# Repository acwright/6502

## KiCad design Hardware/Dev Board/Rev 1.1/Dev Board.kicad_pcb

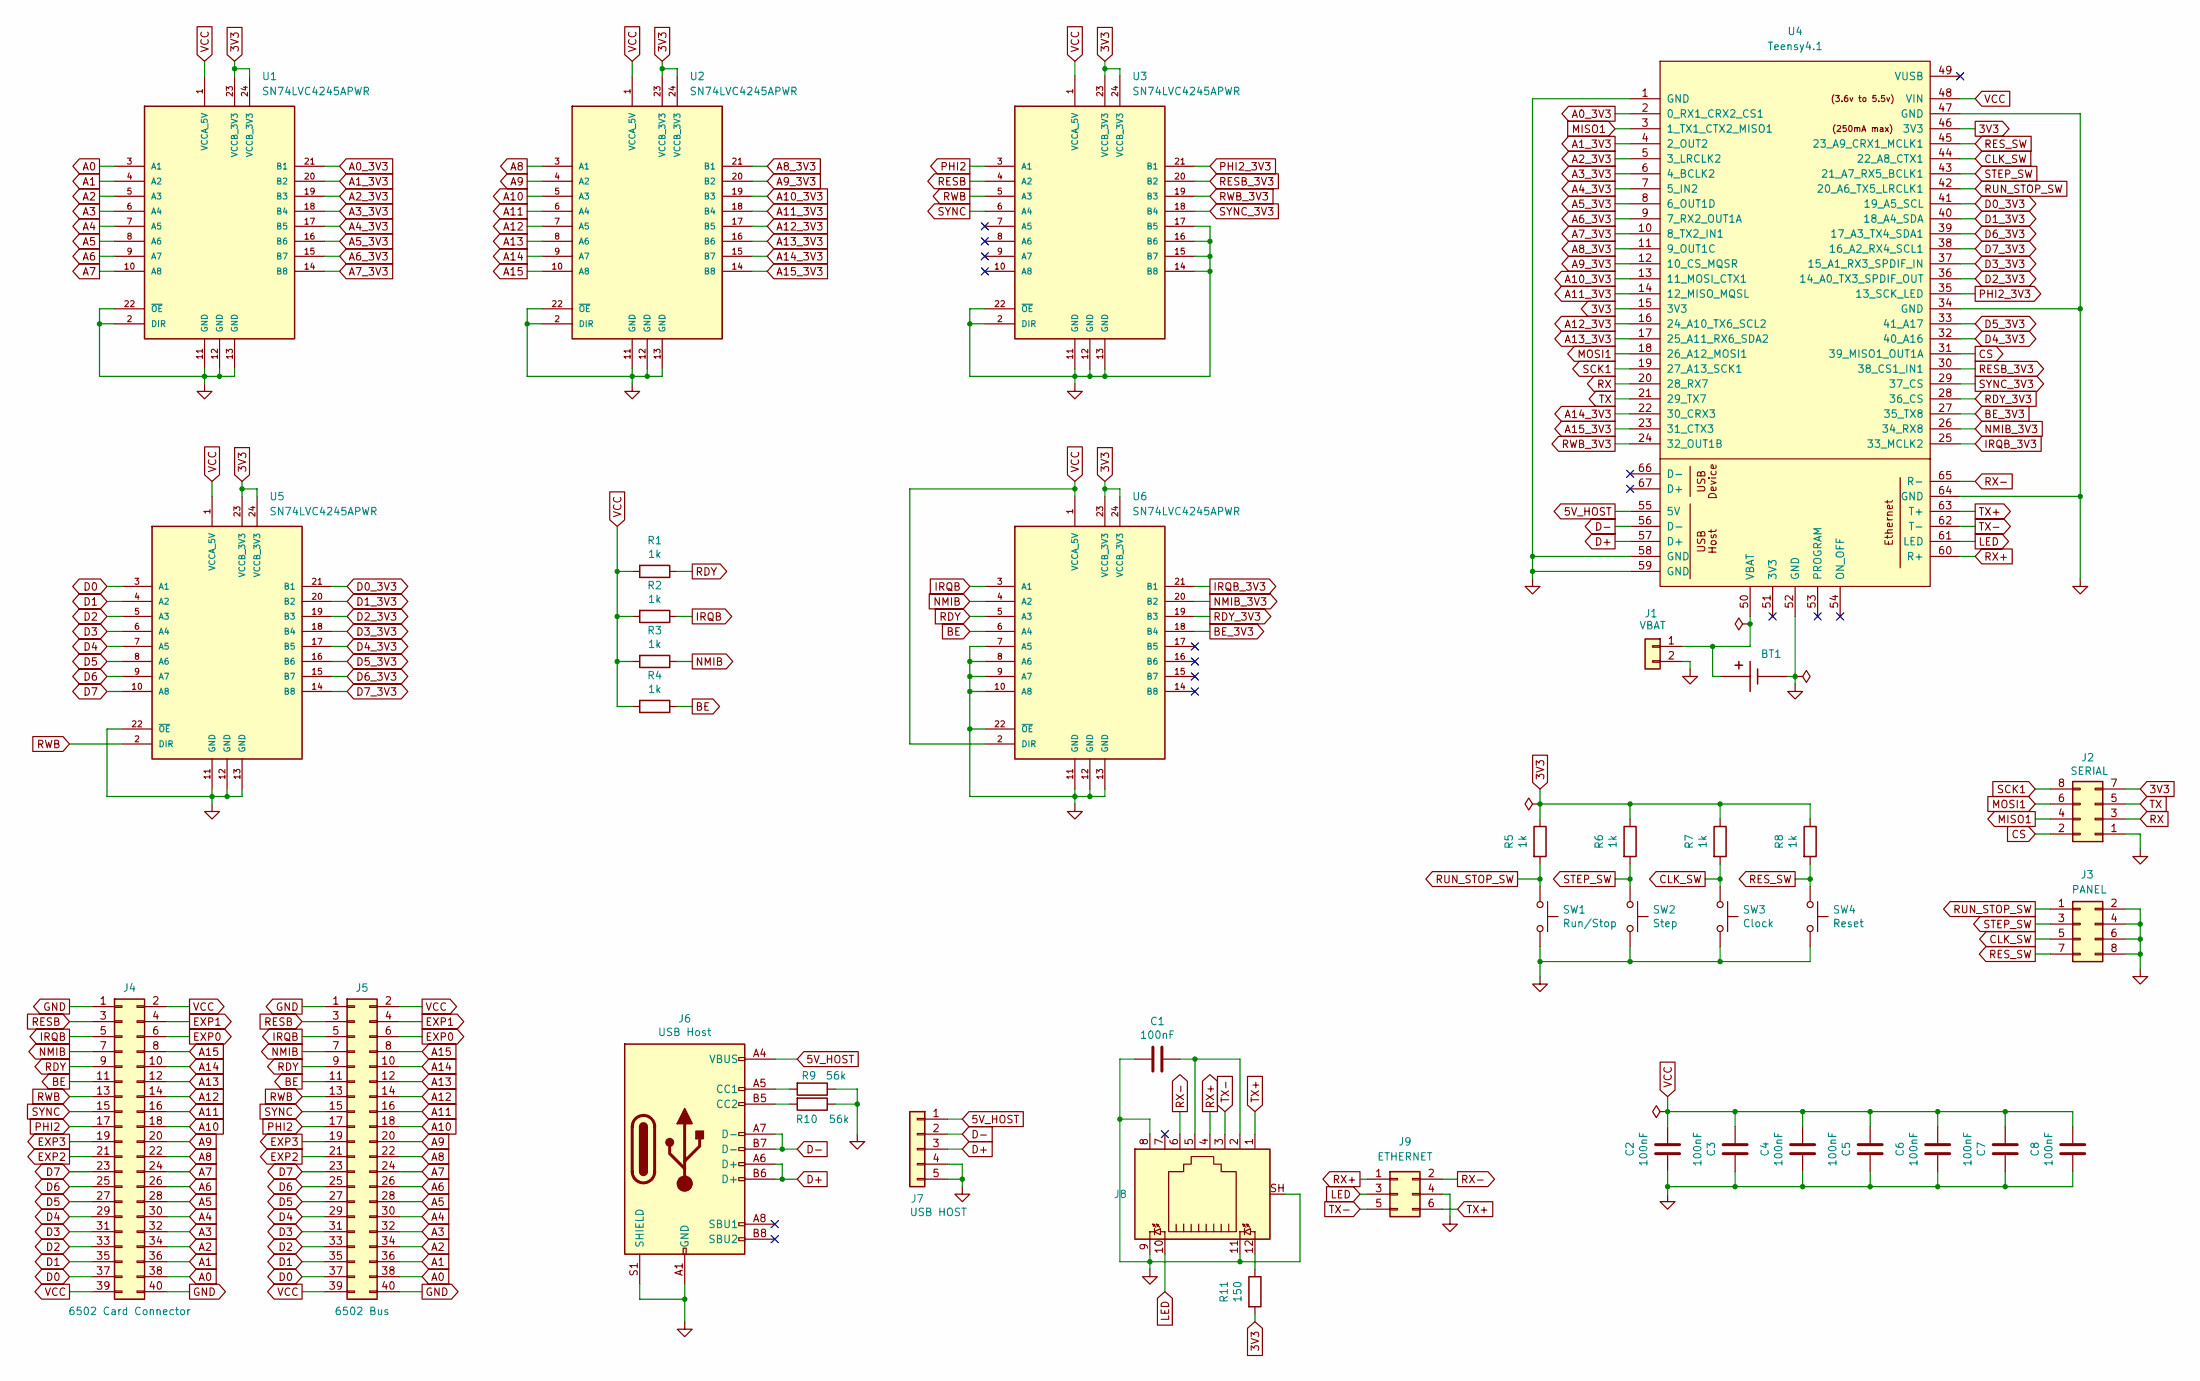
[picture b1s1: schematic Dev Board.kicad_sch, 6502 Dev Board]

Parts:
BT1: BAT-HLD-001-THM; BAT_BAT-HLD-001-THM
C1, C2, C3, C4, C5, C6, C7, C8: 100nF; C_0805_2012Metric; LCSC C49678
J1: VBAT; PinHeader_1x02_P2.54mm_Vertical
J2: SERIAL; PinHeader_2x04_P2.54mm_Vertical
J3: PANEL; PinHeader_2x04_P2.54mm_Vertical
J4: 6502 Card Connector; RHDR40W82P485X254_2X20_5740X93
J5: 6502 Bus; 6502 Bus Connector
J6: USB Host; USB_C_Receptacle_HRO_TYPE-C-31-M-12; LCSC C2988369
J7: USB HOST; PinHeader_1x05_P2.54mm_Vertical
J8: RJ45_LED; J1B1211CCD; MPN J1B1211CCD
J9: ETHERNET; PinHeader_2x03_P2.00mm_Vertical
R1, R2, R3, R4, R5, R6, R7, R8: 1k; R_0805_2012Metric; LCSC C17513
R9, R10: 56k; R_0805_2012Metric; LCSC C169923
R11: 150; R_0805_2012Metric; LCSC C17471
SW1: Run/Stop; SW_TS-1187A-B-A-B; LCSC C318884
SW2: Step; SW_TS-1187A-B-A-B; LCSC C318884
SW3: Clock; SW_TS-1187A-B-A-B; LCSC C318884
SW4: Reset; SW_TS-1187A-B-A-B; LCSC C318884
U1, U2, U3, U5, U6: SN74LVC4245APWR; TSSOP-24_4.4x7.8mm_P0.65mm; LCSC C7859
U4: Teensy4.1; Teensy41

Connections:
3V3: J2.7, R5.1, R6.1, R7.1, R8.1, R11.2, U1.23 (VCCB_3V3), U1.24 (VCCB_3V3), U2.23 (VCCB_3V3), U2.24 (VCCB_3V3), U3.23 (VCCB_3V3), U3.24 (VCCB_3V3), U4.15 (3V3), U4.46 (3V3), U5.23 (VCCB_3V3), U5.24 (VCCB_3V3), U6.23 (VCCB_3V3), U6.24 (VCCB_3V3)
5V_HOST: J6.A4 (VBUS), J6.A9 (VBUS), J6.B4 (VBUS), J6.B9 (VBUS), J7.1, U4.55 (5V)
A0: J4.38, J5.38, U1.3 (A1)
A0_3V3: U1.21 (B1), U4.2 (0_RX1_CRX2_CS1)
A1: J4.36, J5.36, U1.4 (A2)
A1_3V3: U1.20 (B2), U4.4 (2_OUT2)
A2: J4.34, J5.34, U1.5 (A3)
A2_3V3: U1.19 (B3), U4.5 (3_LRCLK2)
A3: J4.32, J5.32, U1.6 (A4)
A3_3V3: U1.18 (B4), U4.6 (4_BCLK2)
A4: J4.30, J5.30, U1.7 (A5)
A4_3V3: U1.17 (B5), U4.7 (5_IN2)
A5: J4.28, J5.28, U1.8 (A6)
A5_3V3: U1.16 (B6), U4.8 (6_OUT1D)
A6: J4.26, J5.26, U1.9 (A7)
A6_3V3: U1.15 (B7), U4.9 (7_RX2_OUT1A)
A7: J4.24, J5.24, U1.10 (A8)
A7_3V3: U1.14 (B8), U4.10 (8_TX2_IN1)
A8: J4.22, J5.22, U2.3 (A1)
A8_3V3: U2.21 (B1), U4.11 (9_OUT1C)
A9: J4.20, J5.20, U2.4 (A2)
A9_3V3: U2.20 (B2), U4.12 (10_CS_MQSR)
A10: J4.18, J5.18, U2.5 (A3)
A10_3V3: U2.19 (B3), U4.13 (11_MOSI_CTX1)
A11: J4.16, J5.16, U2.6 (A4)
A11_3V3: U2.18 (B4), U4.14 (12_MISO_MQSL)
A12: J4.14, J5.14, U2.7 (A5)
A12_3V3: U2.17 (B5), U4.16 (24_A10_TX6_SCL2)
A13: J4.12, J5.12, U2.8 (A6)
A13_3V3: U2.16 (B6), U4.17 (25_A11_RX6_SDA2)
A14: J4.10, J5.10, U2.9 (A7)
A14_3V3: U2.15 (B7), U4.22 (30_CRX3)
A15: J4.8, J5.8, U2.10 (A8)
A15_3V3: U2.14 (B8), U4.23 (31_CTX3)
BE: J4.11, J5.11, R4.1, U6.6 (A4)
BE_3V3: U4.27 (35_TX8), U6.18 (B4)
CLK_SW: J3.5, R7.2, SW3.1, U4.44 (22_A8_CTX1)
CS: J2.2, U4.31 (39_MISO1_OUT1A)
D0: J4.37, J5.37, U5.3 (A1)
D0_3V3: U4.41 (19_A5_SCL), U5.21 (B1)
D1: J4.35, J5.35, U5.4 (A2)
D1_3V3: U4.40 (18_A4_SDA), U5.20 (B2)
D2: J4.33, J5.33, U5.5 (A3)
D2_3V3: U4.36 (14_A0_TX3_SPDIF_OUT), U5.19 (B3)
D3: J4.31, J5.31, U5.6 (A4)
D3_3V3: U4.37 (15_A1_RX3_SPDIF_IN), U5.18 (B4)
D4: J4.29, J5.29, U5.7 (A5)
D4_3V3: U4.32 (40_A16), U5.17 (B5)
D5: J4.27, J5.27, U5.8 (A6)
D5_3V3: U4.33 (41_A17), U5.16 (B6)
D6: J4.25, J5.25, U5.9 (A7)
D6_3V3: U4.39 (17_A3_TX4_SDA1), U5.15 (B7)
D7: J4.23, J5.23, U5.10 (A8)
D7_3V3: U4.38 (16_A2_RX4_SCL1), U5.14 (B8)
D+: J6.A6 (D+), J6.B6 (D+), J7.3, U4.57 (D+)
D-: J6.A7 (D-), J6.B7 (D-), J7.2, U4.56 (D-)
EXP0: J4.6, J5.6
EXP1: J4.4, J5.4
EXP2: J4.21, J5.21
EXP3: J4.19, J5.19
GND: BT1.-, C1.2, C2.2, C3.1, C4.2, C5.1, C6.2, C7.1, C8.2, J1.2, J2.1, J3.2, J3.4, J3.6, J3.8, J4.1, J4.40, J5.1, J5.40, J6.A1 (GND), J6.A12 (GND), J6.B1 (GND), J6.B12 (GND), J6.S1 (SHIELD), J7.4, J7.5, J8.8, J8.9, J8.11, J8.SH, J9.4, R9.1, R10.1, SW1.2, SW2.2, SW3.2, SW4.2, U1.2 (DIR), U1.11 (GND), U1.12 (GND), U1.13 (GND), U1.22 (~OE), U2.2 (DIR), U2.11 (GND), U2.12 (GND), U2.13 (GND), U2.22 (~OE), U3.2 (DIR), U3.11 (GND), U3.12 (GND), U3.13 (GND), U3.14 (B8), U3.15 (B7), U3.16 (B6), U3.17 (B5), U3.22 (~OE), U4.1 (GND), U4.34 (GND), U4.47 (GND), U4.52 (GND), U4.58 (GND), U4.59 (GND), U4.64 (GND), U5.11 (GND), U5.12 (GND), U5.13 (GND), U5.22 (~OE), U6.7 (A5), U6.8 (A6), U6.9 (A7), U6.10 (A8), U6.11 (GND), U6.12 (GND), U6.13 (GND), U6.22 (~OE)
IRQB: J4.5, J5.5, R2.1, U6.3 (A1)
IRQB_3V3: U4.25 (33_MCLK2), U6.21 (B1)
LED: J8.10, J9.3, U4.61 (LED)
MISO1: J2.4, U4.3 (1_TX1_CTX2_MISO1)
MOSI1: J2.6, U4.18 (26_A12_MOSI1)
NMIB: J4.7, J5.7, R3.1, U6.4 (A2)
NMIB_3V3: U4.26 (34_RX8), U6.20 (B2)
unnamed: C1.1, J8.2, J8.5
unnamed: BT1.+, J1.1, U4.50 (VBAT)
unnamed: J6.A5 (CC1), R9.2
unnamed: J6.B5 (CC2), R10.2
unnamed: J8.12, R11.1
PHI2: J4.17, J5.17, U3.3 (A1)
PHI2_3V3: U3.21 (B1), U4.35 (13_SCK_LED)
RDY: J4.9, J5.9, R1.1, U6.5 (A3)
RDY_3V3: U4.28 (36_CS), U6.19 (B3)
RESB: J4.3, J5.3, U3.4 (A2)
RESB_3V3: U3.20 (B2), U4.30 (38_CS1_IN1)
RES_SW: J3.7, R8.2, SW4.1, U4.45 (23_A9_CRX1_MCLK1)
RUN_STOP_SW: J3.1, R5.2, SW1.1, U4.42 (20_A6_TX5_LRCLK1)
RWB: J4.13, J5.13, U3.5 (A3), U5.2 (DIR)
RWB_3V3: U3.19 (B3), U4.24 (32_OUT1B)
RX: J2.3, U4.20 (28_RX7)
RX+: J8.4, J9.1, U4.60 (R+)
RX-: J8.6, J9.2, U4.65 (R-)
SCK1: J2.8, U4.19 (27_A13_SCK1)
STEP_SW: J3.3, R6.2, SW2.1, U4.43 (21_A7_RX5_BCLK1)
SYNC: J4.15, J5.15, U3.6 (A4)
SYNC_3V3: U3.18 (B4), U4.29 (37_CS)
TX: J2.5, U4.21 (29_TX7)
TX+: J8.1, J9.6, U4.63 (T+)
TX-: J8.3, J9.5, U4.62 (T-)
VCC: C2.1, C3.2, C4.1, C5.2, C6.1, C7.2, C8.1, J4.2, J4.39, J5.2, J5.39, R1.2, R2.2, R3.2, R4.2, U1.1 (VCCA_5V), U2.1 (VCCA_5V), U3.1 (VCCA_5V), U4.48 (VIN), U5.1 (VCCA_5V), U6.1 (VCCA_5V), U6.2 (DIR)

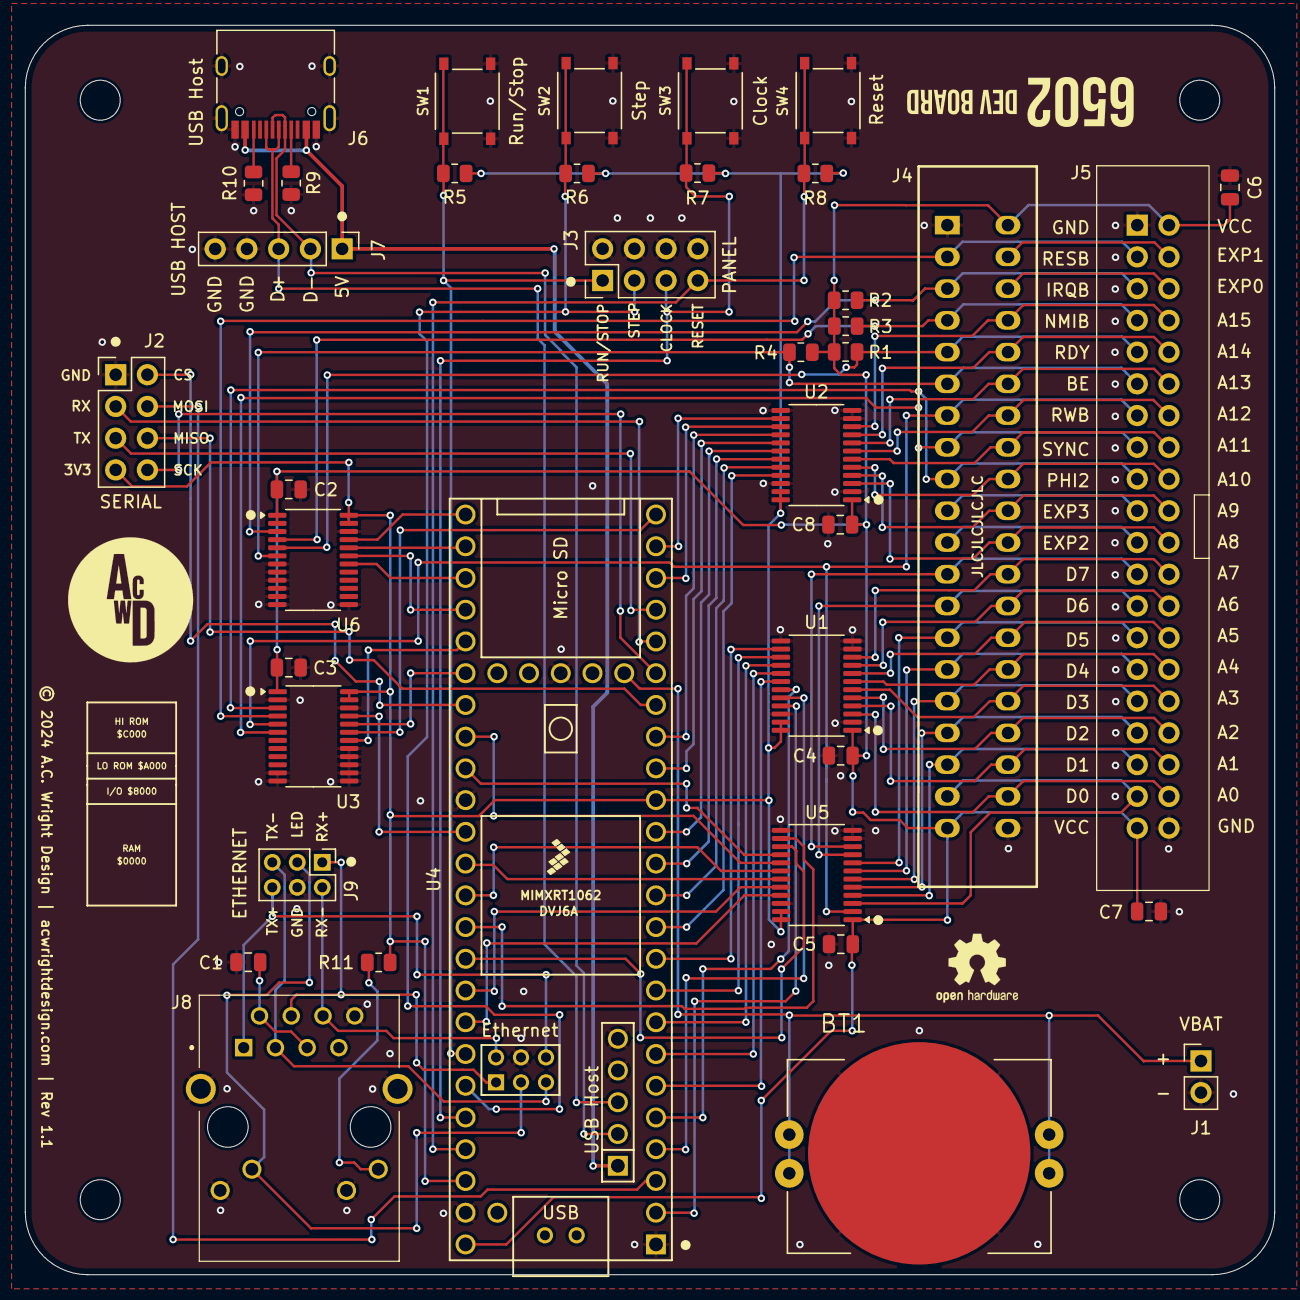
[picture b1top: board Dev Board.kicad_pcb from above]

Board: 2 copper layers, 100.0 x 100.0 mm, 43 parts (0 on the bottom side), 94 nets.

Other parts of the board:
H1, H2, H3, H4: MountingHole; MountingHole_3.2mm_M3

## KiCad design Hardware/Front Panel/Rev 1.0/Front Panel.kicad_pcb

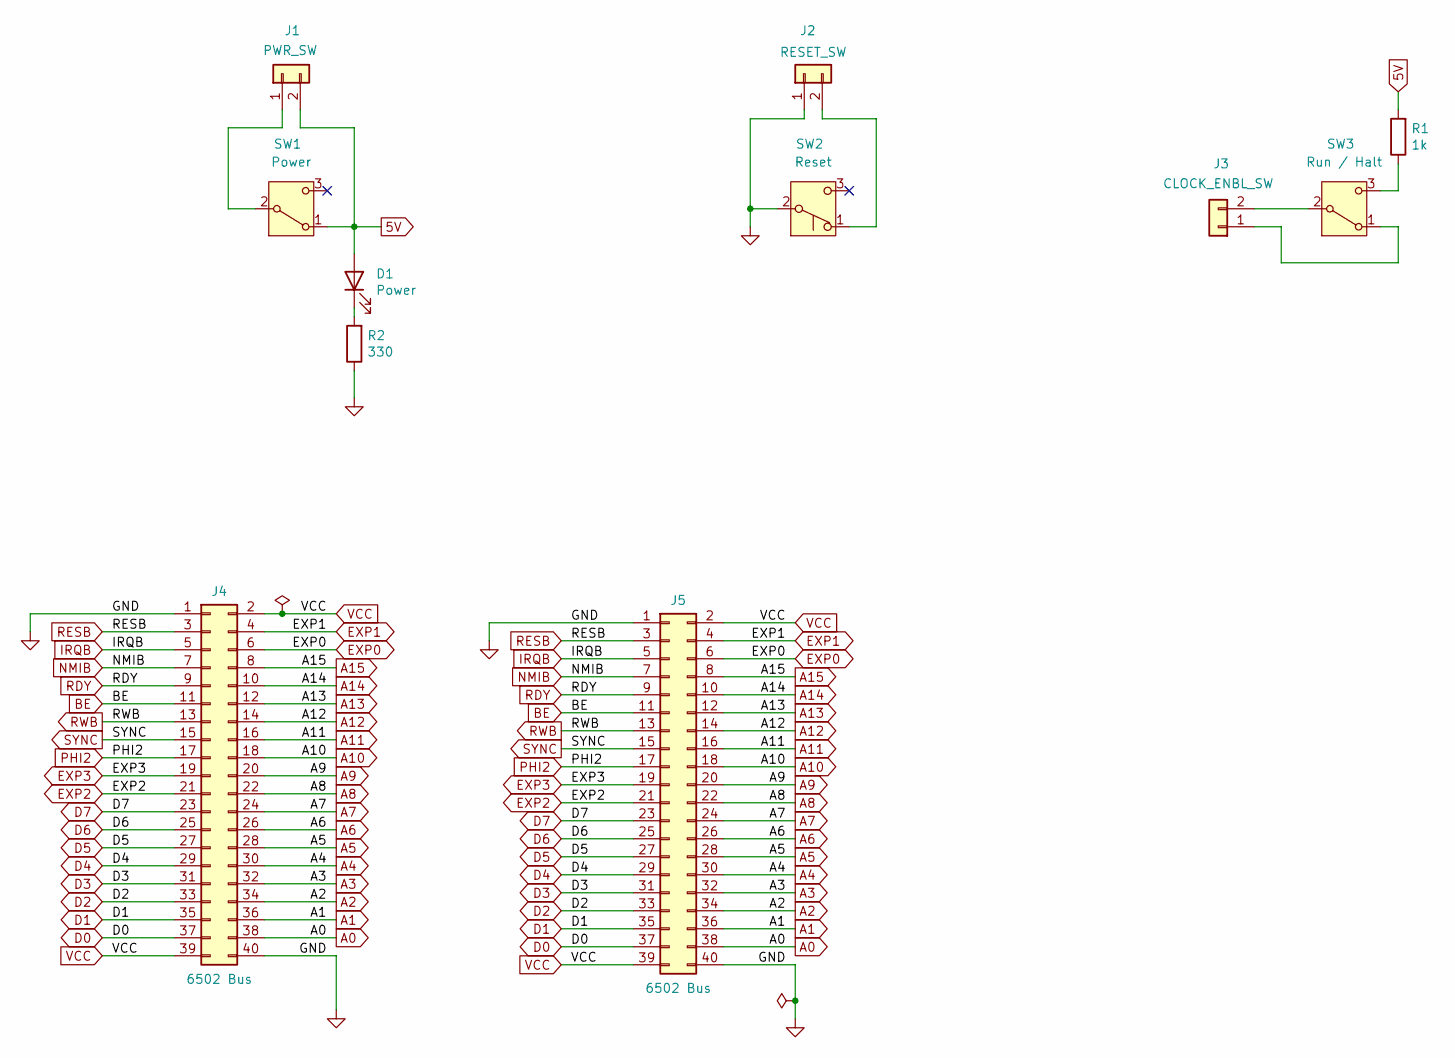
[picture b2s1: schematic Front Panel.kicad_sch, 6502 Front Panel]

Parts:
D1: Power; LED_D3.0mm; LCSC C2297
J1: PWR_SW; JST_XH_B2B-XH-A_1x02_P2.50mm_Vertical; Digikey 455-2247-ND
J2: RESET_SW; JST_XH_B2B-XH-A_1x02_P2.50mm_Vertical; Digikey 455-2247-ND
J3: CLOCK_ENBL_SW; JST_XH_B2B-XH-A_1x02_P2.50mm_Vertical; Digikey 455-2247-ND
J4, J5: 6502 Bus; 6502 Bus Connector
R1: 1k; R_Axial_DIN0207_L6.3mm_D2.5mm_P10.16mm_Horizontal; LCSC C17630
R2: 330; R_Axial_DIN0207_L6.3mm_D2.5mm_P10.16mm_Horizontal; LCSC C17630
SW1: Power; 300SP1J1BLKM2QE; MPN SS12D10; Mouser 612-300SP1J1BLKM2QE
SW2: Reset; 300SP1J1BLKM2QE; MPN SS12D10; Mouser 612-300SP2J1BLKM2QE
SW3: Run / Halt; 300SP1J1BLKM2QE; MPN SS12D10; Mouser 612-300SP1J1BLKM2QE

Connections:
5V: D1.2 (A), J1.2, R1.2, SW1.1 (A)
A0: J4.38, J5.38
A1: J4.36, J5.36
A2: J4.34, J5.34
A3: J4.32, J5.32
A4: J4.30, J5.30
A5: J4.28, J5.28
A6: J4.26, J5.26
A7: J4.24, J5.24
A8: J4.22, J5.22
A9: J4.20, J5.20
A10: J4.18, J5.18
A11: J4.16, J5.16
A12: J4.14, J5.14
A13: J4.12, J5.12
A14: J4.10, J5.10
A15: J4.8, J5.8
BE: J4.11, J5.11
D0: J4.37, J5.37
D1: J4.35, J5.35
D2: J4.33, J5.33
D3: J4.31, J5.31
D4: J4.29, J5.29
D5: J4.27, J5.27
D6: J4.25, J5.25
D7: J4.23, J5.23
EXP0: J4.6, J5.6
EXP1: J4.4, J5.4
EXP2: J4.21, J5.21
EXP3: J4.19, J5.19
GND: J2.1, J4.1, J4.40, J5.1, J5.40, R2.1, SW2.2 (B)
IRQB: J4.5, J5.5
NMIB: J4.7, J5.7
unnamed: D1.1 (K), R2.2
unnamed: J1.1, SW1.2 (B)
unnamed: J2.2, SW2.1 (A)
unnamed: J3.1, SW3.1 (A)
unnamed: J3.2, SW3.2 (B)
unnamed: R1.1, SW3.3 (C)
PHI2: J4.17, J5.17
RDY: J4.9, J5.9
RESB: J4.3, J5.3
RWB: J4.13, J5.13
SYNC: J4.15, J5.15
VCC: J4.2, J4.39, J5.2, J5.39

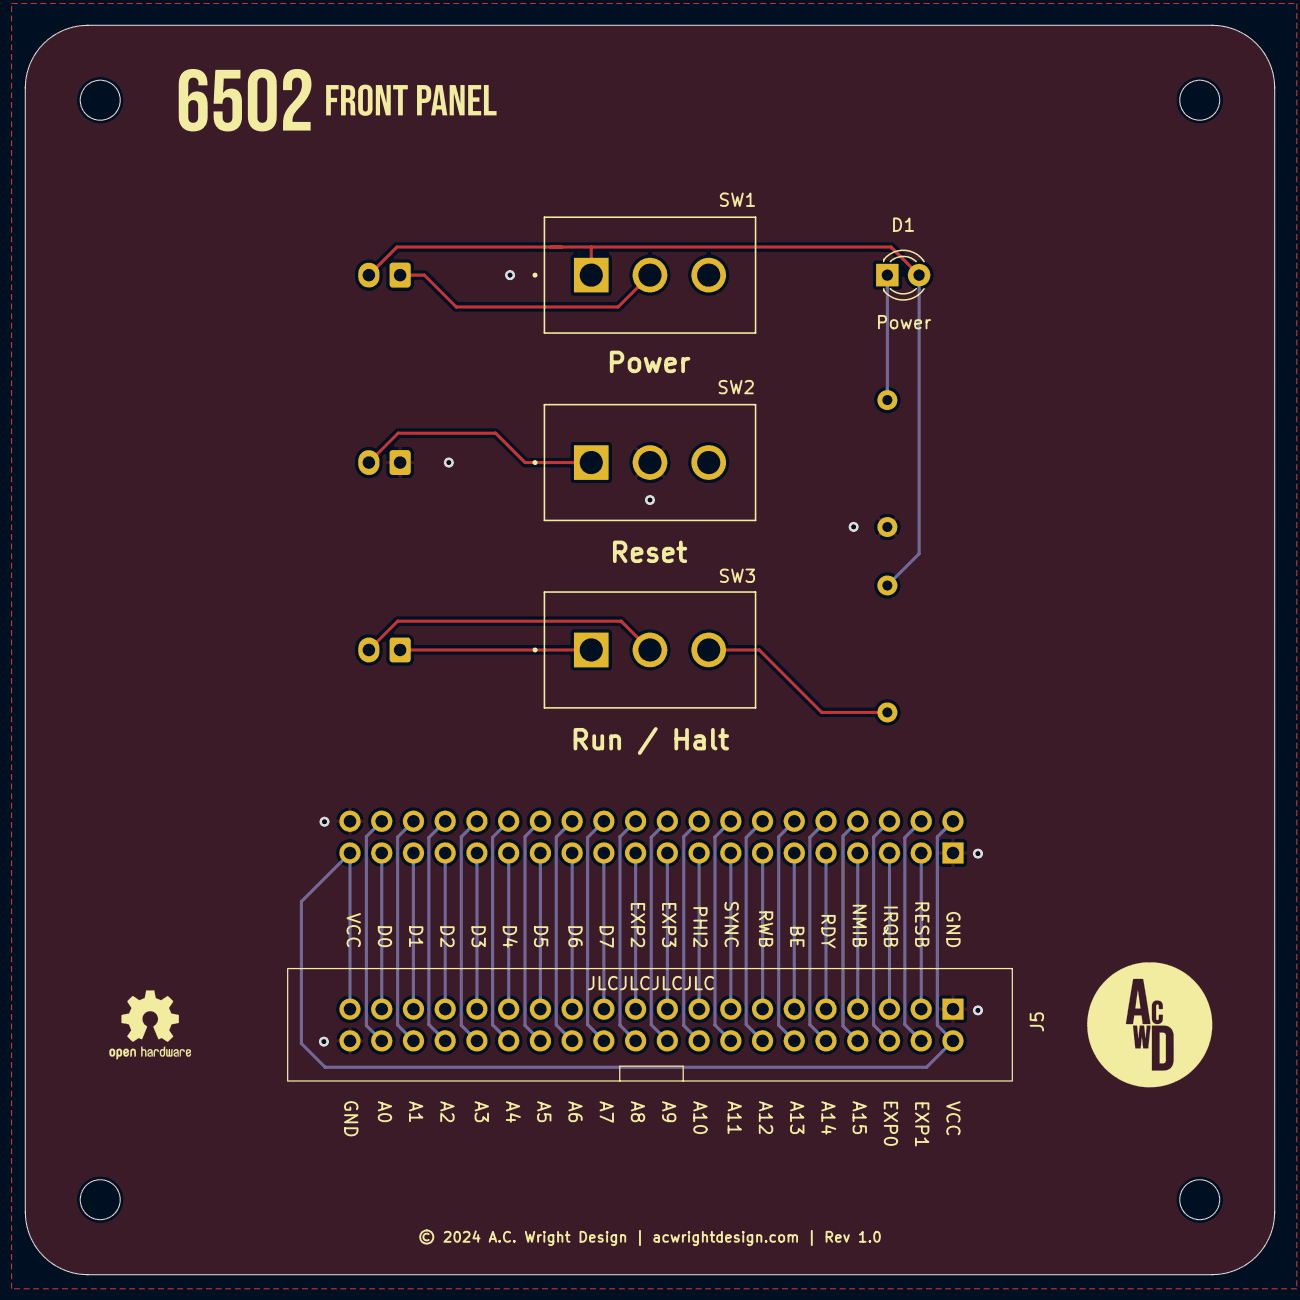
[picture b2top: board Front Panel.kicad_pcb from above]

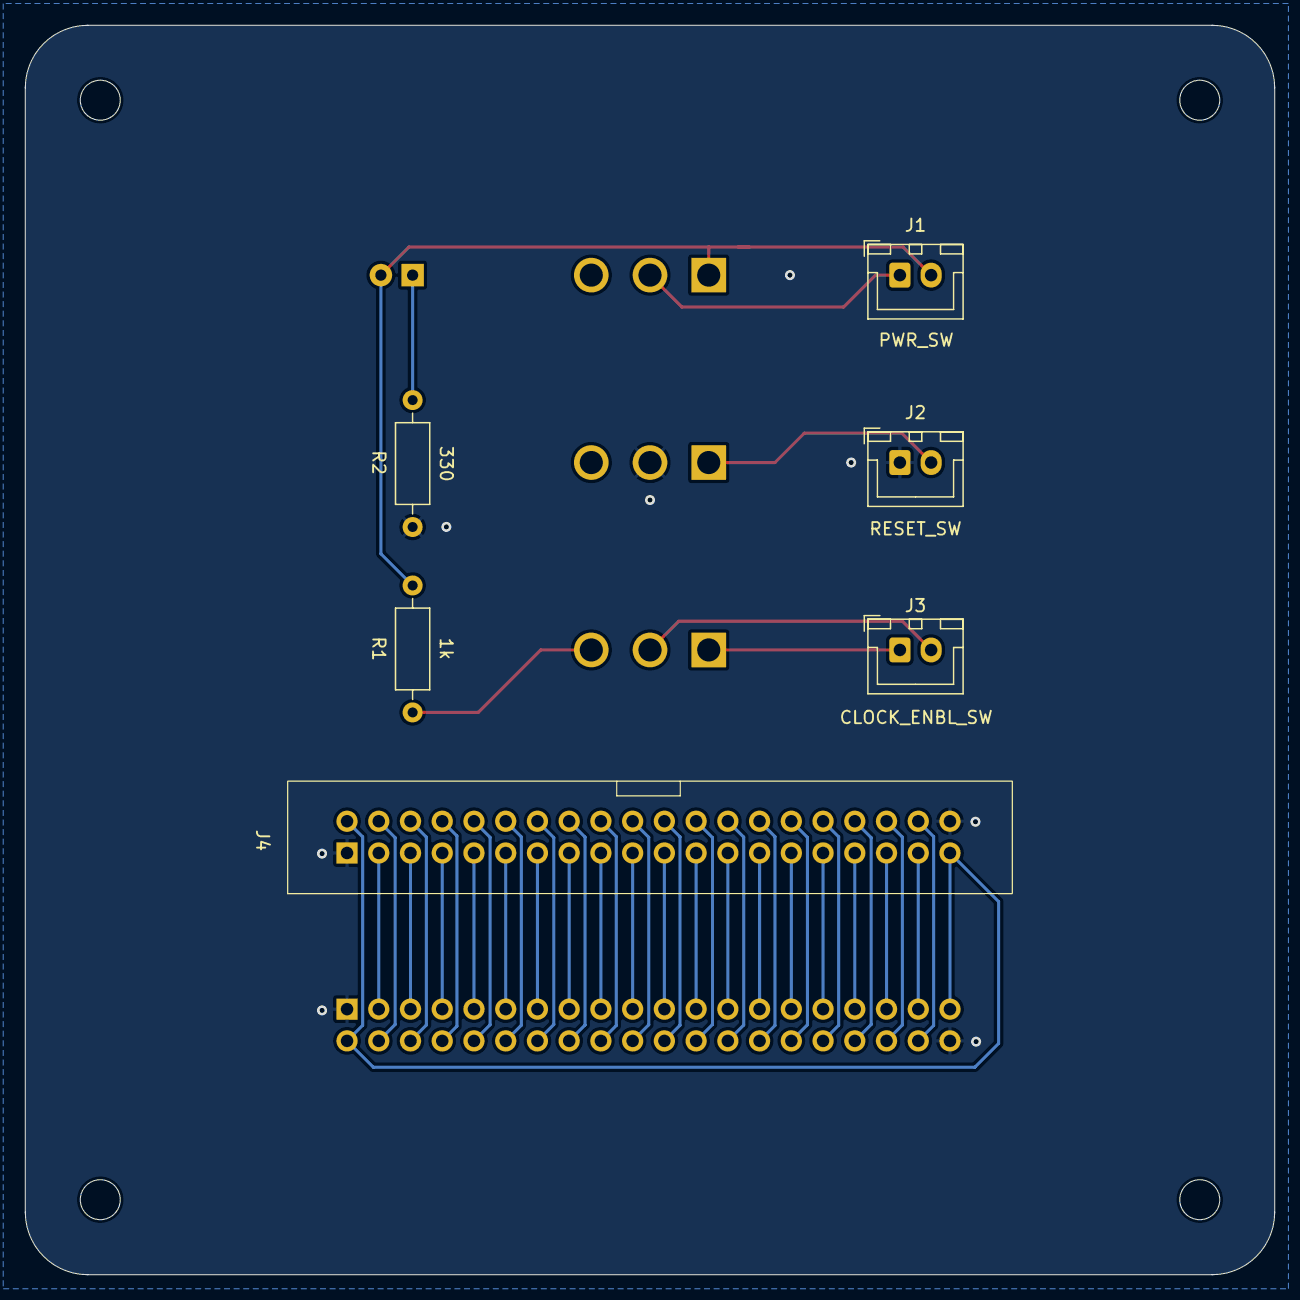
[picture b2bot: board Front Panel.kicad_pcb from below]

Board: 2 copper layers, 100.0 x 100.0 mm, 15 parts (6 on the bottom side), 45 nets.

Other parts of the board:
H1, H2, H3, H4: MountingHole; MountingHole_3.2mm_M3

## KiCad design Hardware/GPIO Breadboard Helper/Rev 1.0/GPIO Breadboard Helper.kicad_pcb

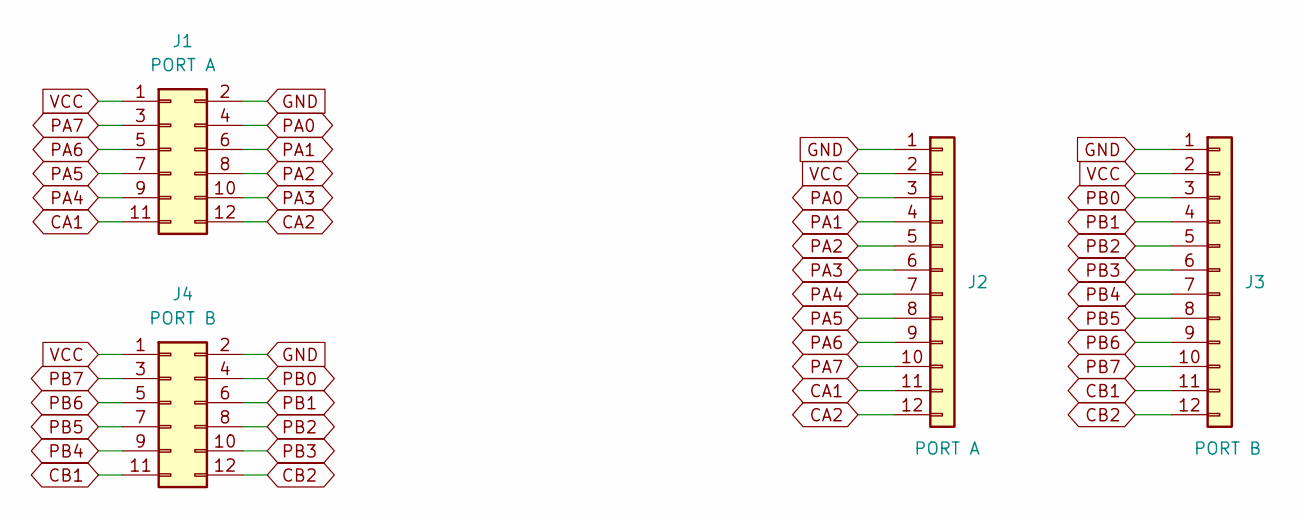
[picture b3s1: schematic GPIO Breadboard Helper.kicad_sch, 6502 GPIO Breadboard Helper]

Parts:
J1: PORT A; 6502 GPIO Connector
J2: PORT A; PinHeader_1x12_P2.54mm_Vertical
J3: PORT B; PinHeader_1x12_P2.54mm_Vertical
J4: PORT B; 6502 GPIO Connector

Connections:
CA1: J1.11, J2.11
CA2: J1.12, J2.12
CB1: J3.11, J4.11
CB2: J3.12, J4.12
GND: J1.2, J2.1, J3.1, J4.2
PA0: J1.4, J2.3
PA1: J1.6, J2.4
PA2: J1.8, J2.5
PA3: J1.10, J2.6
PA4: J1.9, J2.7
PA5: J1.7, J2.8
PA6: J1.5, J2.9
PA7: J1.3, J2.10
PB0: J3.3, J4.4
PB1: J3.4, J4.6
PB2: J3.5, J4.8
PB3: J3.6, J4.10
PB4: J3.7, J4.9
PB5: J3.8, J4.7
PB6: J3.9, J4.5
PB7: J3.10, J4.3
VCC: J1.1, J2.2, J3.2, J4.1

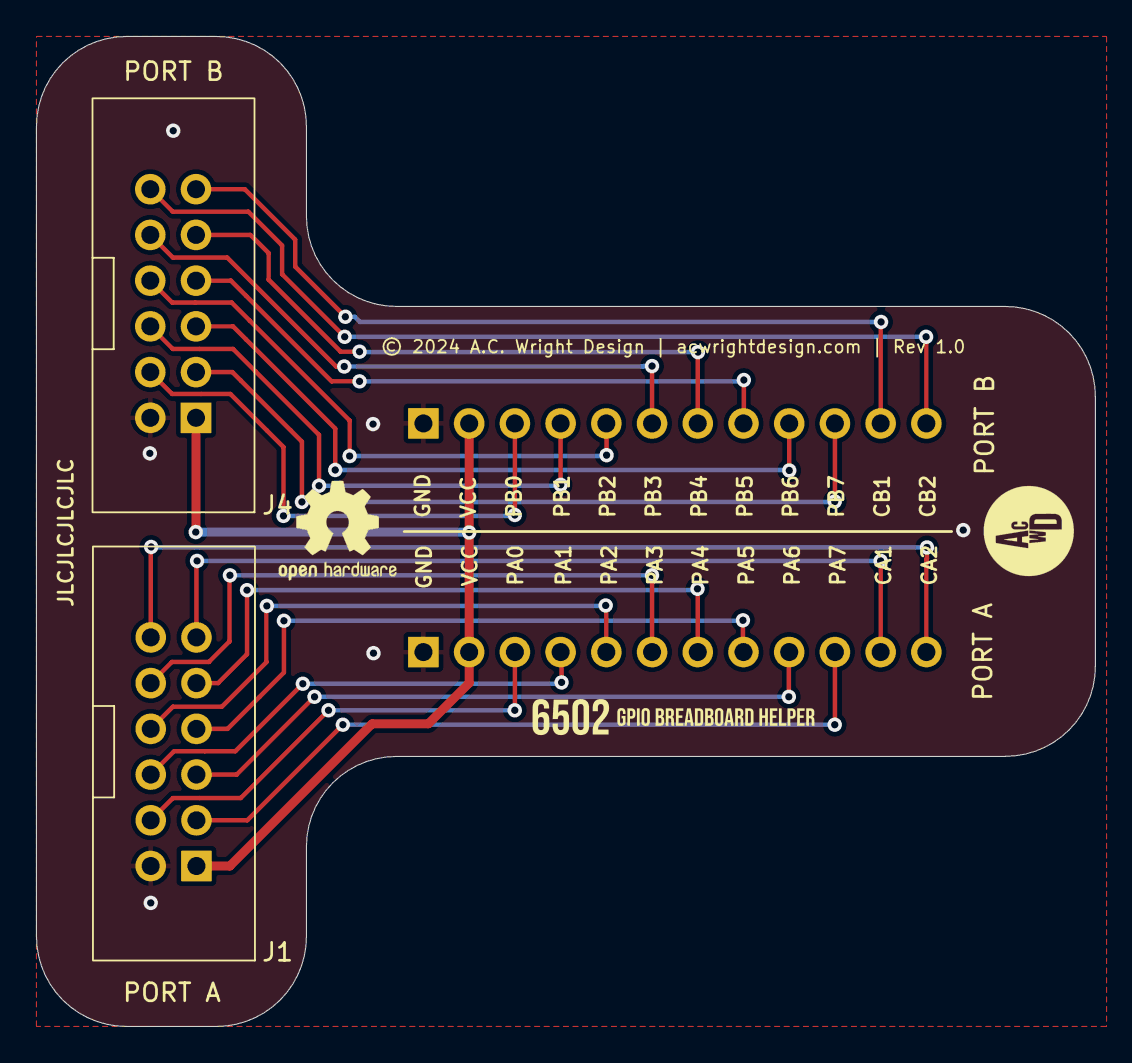
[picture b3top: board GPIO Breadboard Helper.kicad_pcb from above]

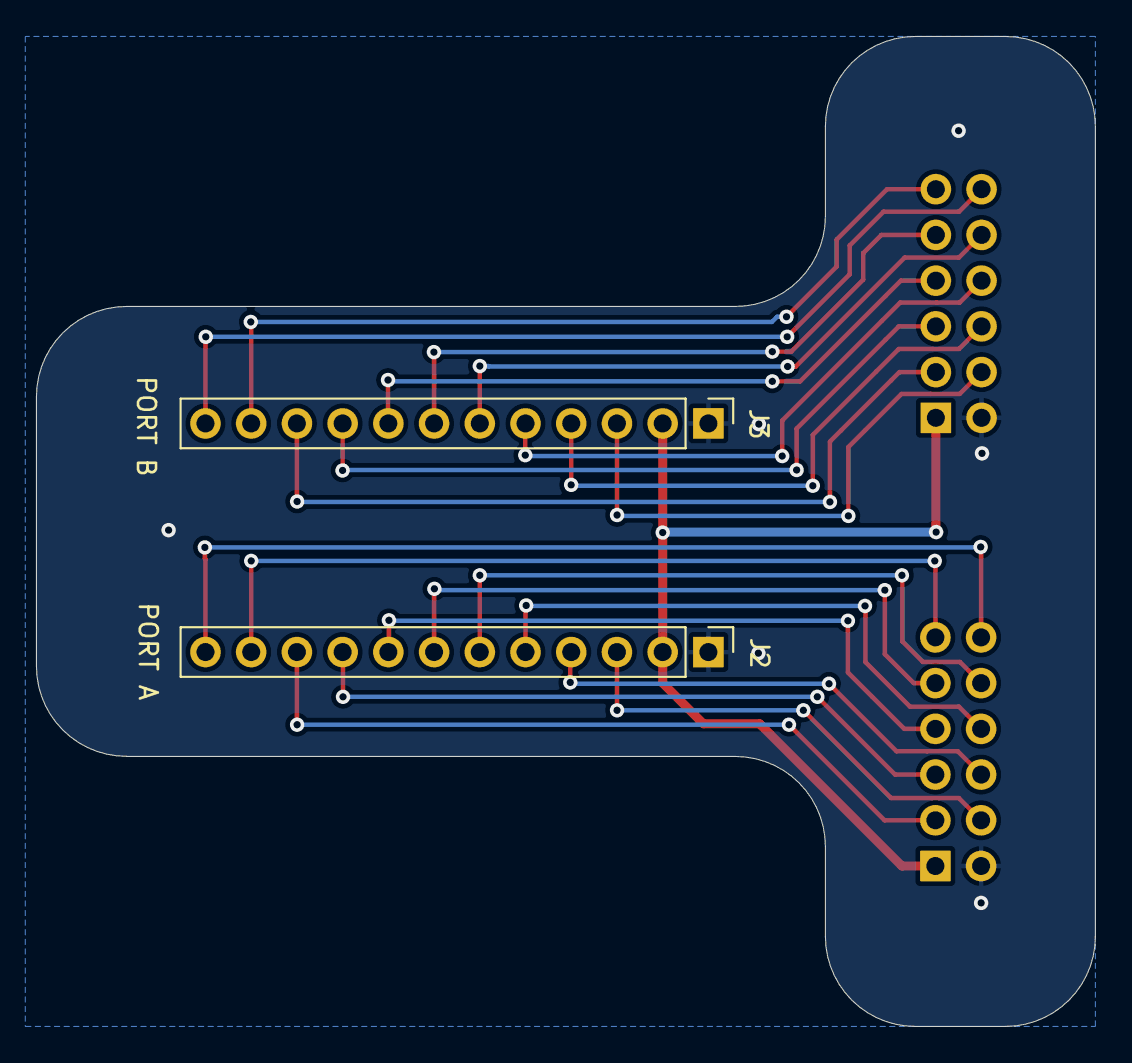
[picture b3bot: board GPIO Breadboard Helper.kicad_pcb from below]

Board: 2 copper layers, 58.8 x 55.0 mm, 4 parts (2 on the bottom side), 22 nets.

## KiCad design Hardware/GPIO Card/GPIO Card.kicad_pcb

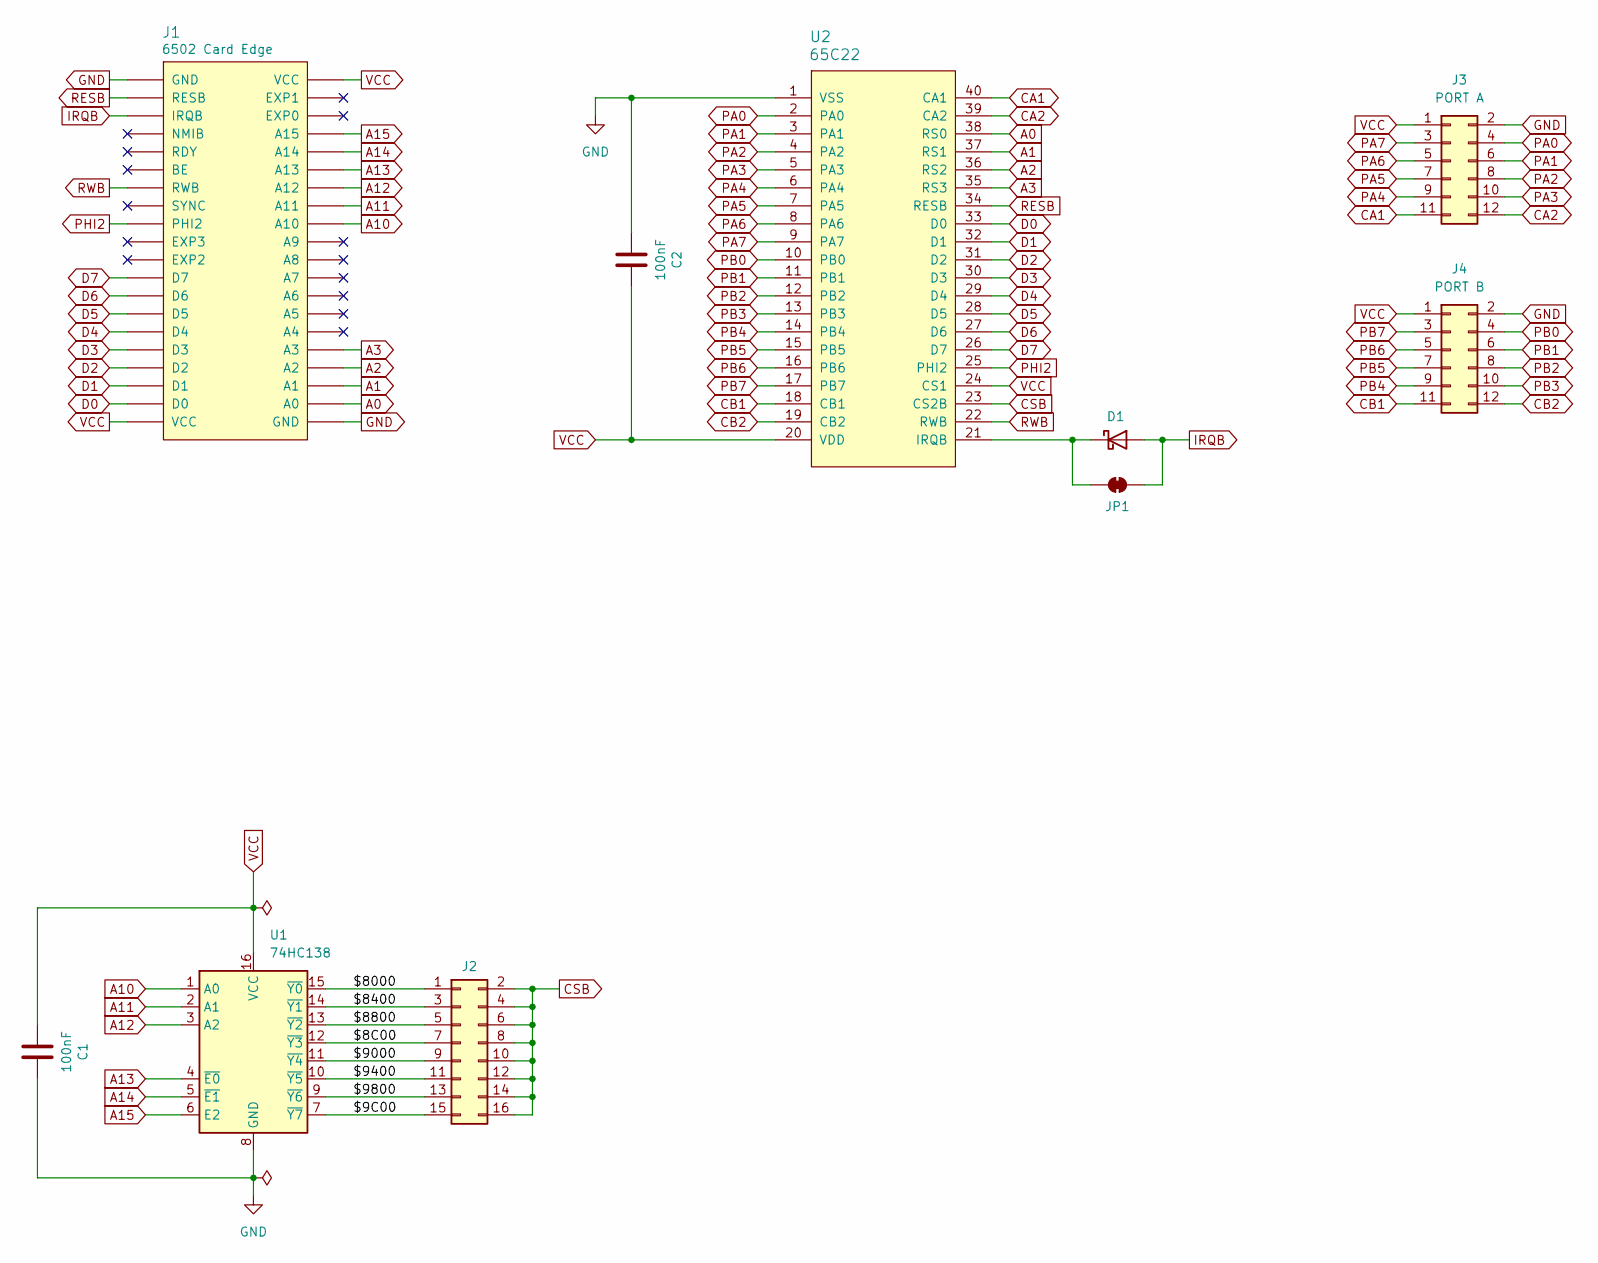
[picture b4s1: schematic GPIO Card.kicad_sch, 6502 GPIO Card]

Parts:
C1, C2: 100nF; C_0805_2012Metric; LCSC C49678
D1: D_Schottky; D_DO-35_SOD27_P7.62mm_Horizontal
J1: 6502 Card Edge
J2: Conn_02x08_Odd_Even; PinHeader_2x08_P2.54mm_Vertical
J3: PORT A; PinHeader_2x06_P2.54mm_Vertical
J4: PORT B; PinHeader_2x06_P2.54mm_Vertical
JP1: SolderJumper_2_Bridged; SolderJumper-2_P1.3mm_Bridged_RoundedPad1.0x1.5mm
U1: 74HC138; SOIC-16_3.9x9.9mm_P1.27mm; LCSC C5602
U2: 65C22; DIP-40_W15.24mm_Socket_LongPads

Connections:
/$8C00: J2.7, U1.12 (~Y3)
/$9C00: J2.15, U1.7 (~Y7)
/$8000: J2.1, U1.15 (~Y0)
/$8400: J2.3, U1.14 (~Y1)
/$8800: J2.5, U1.13 (~Y2)
/$9000: J2.9, U1.11 (~Y4)
/$9400: J2.11, U1.10 (~Y5)
/$9800: J2.13, U1.9 (~Y6)
A0: J1.A0, U2.38 (RS0)
A1: J1.A1, U2.37 (RS1)
A2: J1.A2, U2.36 (RS2)
A3: J1.A3, U2.35 (RS3)
A10: J1.A10, U1.1 (A0)
A11: J1.A11, U1.2 (A1)
A12: J1.A12, U1.3 (A2)
A13: J1.A13, U1.4 (~E0)
A14: J1.A14, U1.5 (~E1)
A15: J1.A15, U1.6 (E2)
CA1: J3.11, U2.40 (CA1)
CA2: J3.12, U2.39 (CA2)
CB1: J4.11, U2.18 (CB1)
CB2: J4.12, U2.19 (CB2)
CSB: J2.2, J2.4, J2.6, J2.8, J2.10, J2.12, J2.14, J2.16, U2.23 (CS2B)
D0: J1.D0, U2.33 (D0)
D1: J1.D1, U2.32 (D1)
D2: J1.D2, U2.31 (D2)
D3: J1.D3, U2.30 (D3)
D4: J1.D4, U2.29 (D4)
D5: J1.D5, U2.28 (D5)
D6: J1.D6, U2.27 (D6)
D7: J1.D7, U2.26 (D7)
GND: C1.2, C2.1, J1.GND, J3.2, J4.2, U1.8 (GND), U2.1 (VSS)
IRQB: D1.2 (A), J1.IRQB, JP1.2 (B)
unnamed: D1.1 (K), JP1.1 (A), U2.21 (IRQB)
PA0: J3.4, U2.2 (PA0)
PA1: J3.6, U2.3 (PA1)
PA2: J3.8, U2.4 (PA2)
PA3: J3.10, U2.5 (PA3)
PA4: J3.9, U2.6 (PA4)
PA5: J3.7, U2.7 (PA5)
PA6: J3.5, U2.8 (PA6)
PA7: J3.3, U2.9 (PA7)
PB0: J4.4, U2.10 (PB0)
PB1: J4.6, U2.11 (PB1)
PB2: J4.8, U2.12 (PB2)
PB3: J4.10, U2.13 (PB3)
PB4: J4.9, U2.14 (PB4)
PB5: J4.7, U2.15 (PB5)
PB6: J4.5, U2.16 (PB6)
PB7: J4.3, U2.17 (PB7)
PHI2: J1.PHI2, U2.25 (PHI2)
RESB: J1.RESB, U2.34 (RESB)
RWB: J1.RWB, U2.22 (RWB)
VCC: C1.1, C2.2, J1.VCC, J3.1, J4.1, U1.16 (VCC), U2.20 (VDD), U2.24 (CS1)

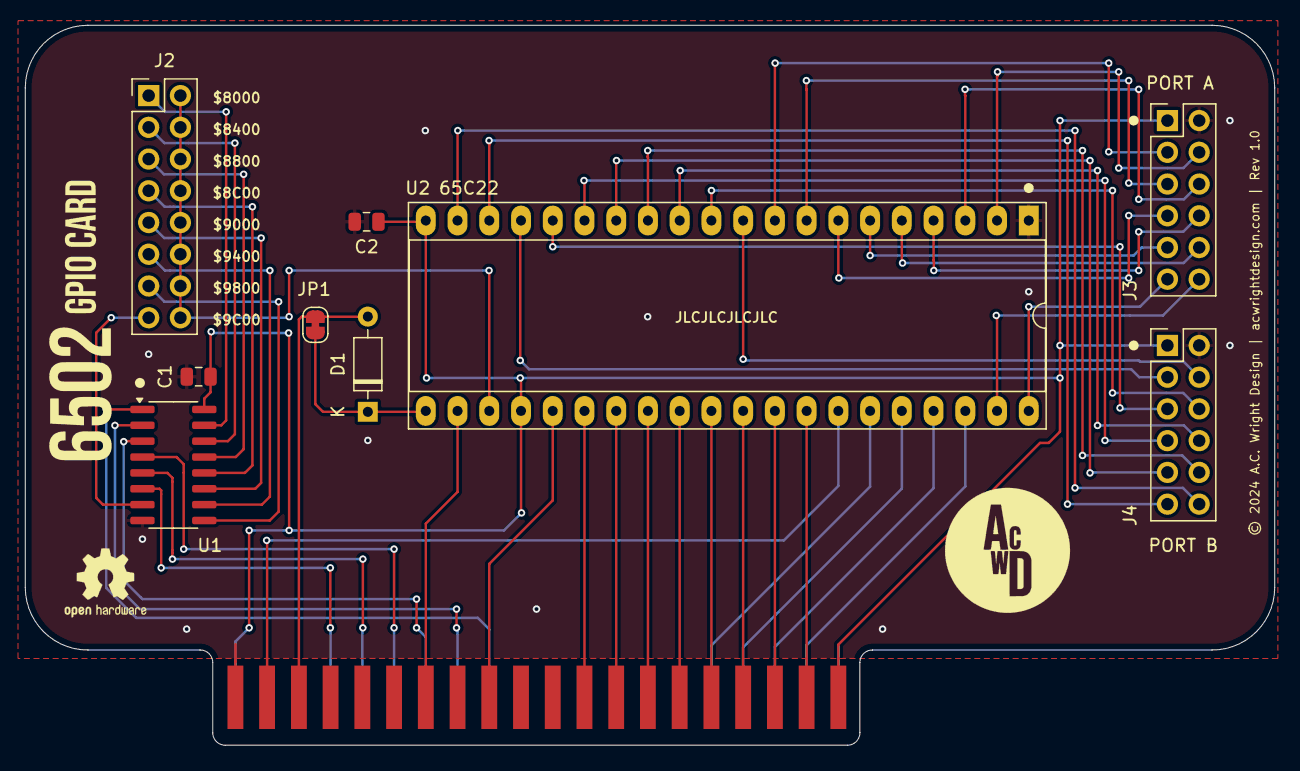
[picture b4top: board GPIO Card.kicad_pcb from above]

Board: 2 copper layers, 100.0 x 57.6 mm, 10 parts (0 on the bottom side), 54 nets.

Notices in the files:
Hardware/Dev Board/Rev 1.1/Dev Board.kicad_pcb:
© 2024 A.C. Wright Design | acwrightdesign.com | Rev 1.1
Hardware/Front Panel/Rev 1.0/Front Panel.kicad_pcb:
© 2024 A.C. Wright Design | acwrightdesign.com | Rev 1.0
